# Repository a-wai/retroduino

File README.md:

# RetroDuino

The RetroDuino is an attempt at designing and building an 8-bit microcomputer,
using a 6502 processor, and offering a number of I/O options, as commonly found
on Arduino boards.

## Features

This 130x75mm SBC (Single Board Computer) provides a UART interface, an I2C bus#
and 24 GPIOs.

It includes 31kB of SRAM, 32kB of flash memory (mounted on a ZIF socket for
easier programming), and runs at 8MHz.

## Internals

The RetroDuino includes:

- 1 65C02 processsor w/ 8MHz oscillator
- 1 GAL22V10 for address decoding logic
- 1 AS6C62256 32kB SRAM
- 1 SST39SF010/020/040 flash memory, of which only 32kB is used
- 1 SCC2691 UART controller
- 1 PCF8584 I2C controller
- 1 82C55A peripheral interface providing 24 GPIO lines

It can be powered using a 7-24V DC power supply.

## Current status

This project is still in its infancy: hardware design is complete, but not
tested yet. The next steps are:

- [ ] program and test the GAL logic
- [ ] prototype a flash programmer (probably using a STM32 board)
- [ ] order the board and build the project
- [ ] write the software

## Why?

Why go through so much pain, when hundreds of microcontroller boards are
widely available and so cheap? Because... Well, it's fun!

And as a positive side effect, this is a good way to learn a lot about the
internals of modern microcontrollers, or computers in general.

## Licensing

Copyright 2019, Arnaud Ferraris.

This documentation describes Open Hardware and is licensed under the
CERN OHL v.1.2.

You may redistribute and modify this documentation under the terms of the
[CERN OHL v.1.2](http://ohwr.org/cernohl). This documentation is distributed
WITHOUT ANY EXPRESS OR IMPLIED WARRANTY, INCLUDING OF MERCHANTABILITY,
SATISFACTORY QUALITY AND FITNESS FOR A PARTICULAR PURPOSE.

Please see the CERN OHL v.1.2 for applicable conditions.

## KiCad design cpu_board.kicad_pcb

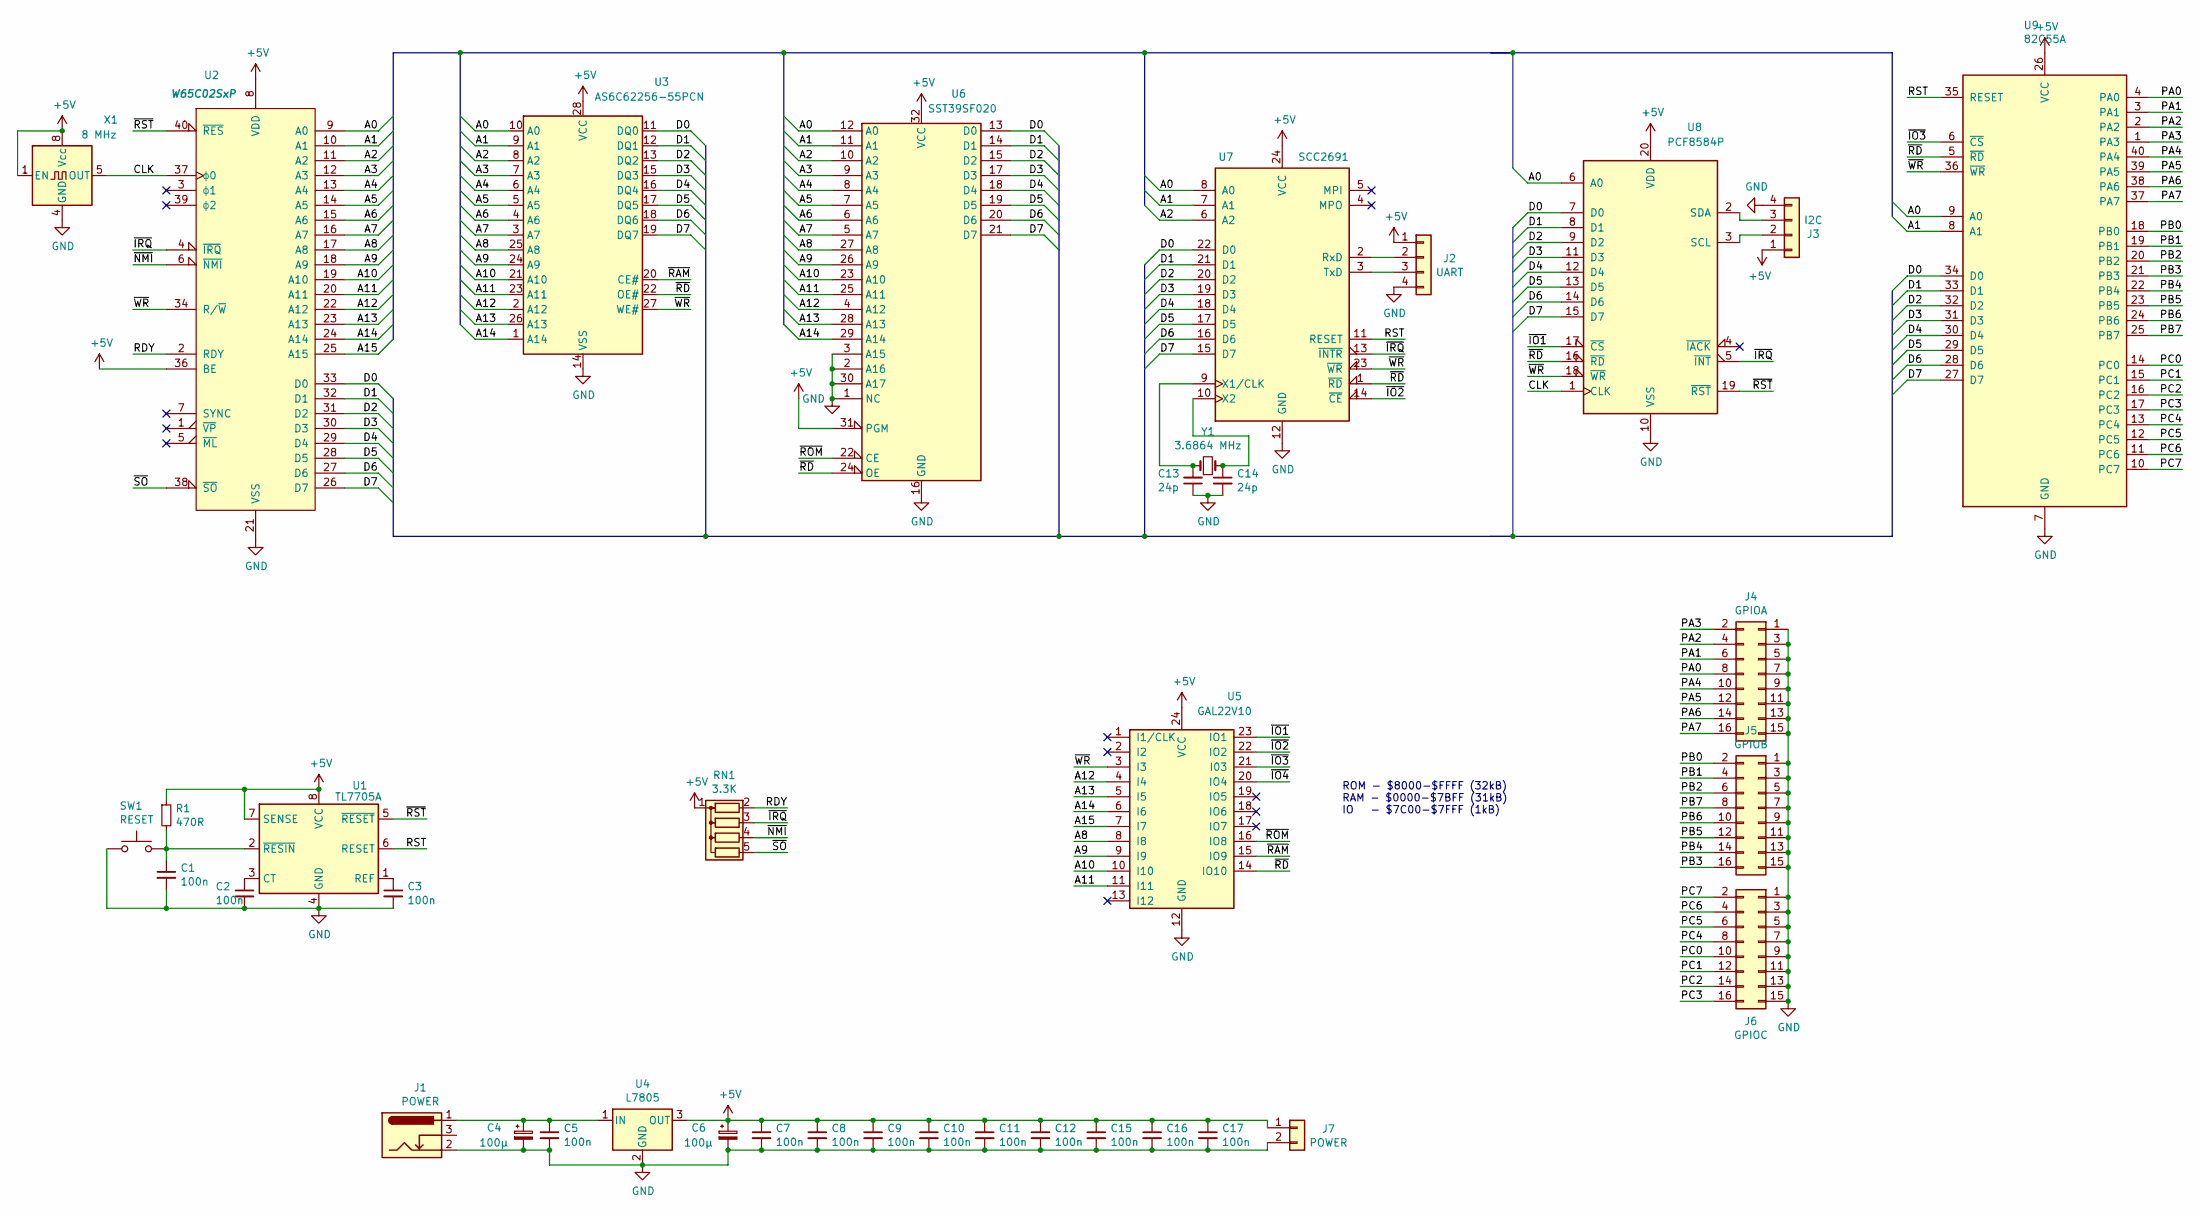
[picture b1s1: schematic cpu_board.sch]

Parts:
C1, C2, C3, C5, C7, C8, C9, C10, C11, C12, C15, C16, C17: 100n; C_Disc_D3.8mm_W2.6mm_P2.50mm
C4, C6: 100µ; CP_Radial_D6.3mm_P2.50mm
C13, C14: 24p; C_Disc_D3.8mm_W2.6mm_P2.50mm
J1: POWER; BarrelJack_Horizontal
J2: UART; PinHeader_1x04_P2.54mm_Vertical
J3: I2C; PinHeader_1x04_P2.54mm_Vertical
J4: GPIOA; PinHeader_2x08_P2.54mm_Vertical
J5: GPIOB; PinHeader_2x08_P2.54mm_Vertical
J6: GPIOC; PinHeader_2x08_P2.54mm_Vertical
J7: POWER; PinHeader_1x02_P2.54mm_Vertical
R1: 470R; R_Axial_DIN0309_L9.0mm_D3.2mm_P12.70mm_Horizontal
RN1: 3.3K; R_Array_SIP5
SW1: RESET; SW_PUSH_6mm
U1: TL7705A; DIP-8_W7.62mm_Socket_LongPads
U2: W65C02SxP; DIP-40_W15.24mm_Socket_LongPads
U3: AS6C62256-55PCN; DIP-28_W15.24mm_Socket_LongPads
U4: L7805; TO-220-3_Vertical
U5: GAL22V10; DIP-24_W7.62mm_Socket_LongPads
U6: SST39SF020; DIP_Socket-32_W11.9_W12.7_W15.24_W17.78_W18.5_3M_232-1285-0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
U7: SCC2691; DIP-24_W7.62mm_Socket_LongPads
U8: PCF8584P; DIP-20_W7.62mm_Socket_LongPads
U9: 82C55A; DIP-40_W15.24mm_Socket_LongPads
X1: 8 MHz; Oscillator_DIP-8_LargePads
Y1: 3.6864 MHz; Crystal_HC49-U_Vertical

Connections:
+5V: C6.1, C7.1, C8.1, C9.1, C10.1, C11.1, C12.1, C15.1, C16.1, C17.1, J2.1, J3.1, J7.1, R1.1, RN1.1 (common), U1.7 (SENSE), U1.8 (VCC), U2.8 (VDD), U2.36 (BE), U3.28 (VCC), U4.3 (OUT), U5.24 (VCC), U6.31 (PGM), U6.32 (VCC), U7.24 (VCC), U8.20 (VDD), U9.26 (VCC), X1.1 (EN), X1.8 (Vcc)
/A0: U2.9 (A0), U3.10 (A0), U6.12 (A0), U7.8 (A0), U8.6 (A0), U9.9 (A0)
/A1: U2.10 (A1), U3.9 (A1), U6.11 (A1), U7.7 (A1), U9.8 (A1)
/A2: U2.11 (A2), U3.8 (A2), U6.10 (A2), U7.6 (A2)
/A3: U2.12 (A3), U3.7 (A3), U6.9 (A3)
/A4: U2.13 (A4), U3.6 (A4), U6.8 (A4)
/A5: U2.14 (A5), U3.5 (A5), U6.7 (A5)
/A6: U2.15 (A6), U3.4 (A6), U6.6 (A6)
/A7: U2.16 (A7), U3.3 (A7), U6.5 (A7)
/A8: U2.17 (A8), U3.25 (A8), U5.8 (I8), U6.27 (A8)
/A9: U2.18 (A9), U3.24 (A9), U5.9 (I9), U6.26 (A9)
/A10: U2.19 (A10), U3.21 (A10), U5.10 (I10), U6.23 (A10)
/A11: U2.20 (A11), U3.23 (A11), U5.11 (I11), U6.25 (A11)
/A12: U2.22 (A12), U3.2 (A12), U5.4 (I4), U6.4 (A12)
/A13: U2.23 (A13), U3.26 (A13), U5.5 (I5), U6.28 (A13)
/A14: U2.24 (A14), U3.1 (A14), U5.6 (I6), U6.29 (A14)
/A15: U2.25 (A15), U5.7 (I7)
/CLK: U2.37 (ϕ0), U8.1 (CLK), X1.5 (OUT)
/D0: U2.33 (D0), U3.11 (DQ0), U6.13 (D0), U7.22 (D0), U8.7 (D0), U9.34 (D0)
/D1: U2.32 (D1), U3.12 (DQ1), U6.14 (D1), U7.21 (D1), U8.8 (D1), U9.33 (D1)
/D2: U2.31 (D2), U3.13 (DQ2), U6.15 (D2), U7.20 (D2), U8.9 (D2), U9.32 (D2)
/D3: U2.30 (D3), U3.15 (DQ3), U6.17 (D3), U7.19 (D3), U8.11 (D3), U9.31 (D3)
/D4: U2.29 (D4), U3.16 (DQ4), U6.18 (D4), U7.18 (D4), U8.12 (D4), U9.30 (D4)
/D5: U2.28 (D5), U3.17 (DQ5), U6.19 (D5), U7.17 (D5), U8.13 (D5), U9.29 (D5)
/D6: U2.27 (D6), U3.18 (DQ6), U6.20 (D6), U7.16 (D6), U8.14 (D6), U9.28 (D6)
/D7: U2.26 (D7), U3.19 (DQ7), U6.21 (D7), U7.15 (D7), U8.15 (D7), U9.27 (D7)
/PA0: J4.8, U9.4 (PA0)
/PA1: J4.6, U9.3 (PA1)
/PA2: J4.4, U9.2 (PA2)
/PA3: J4.2, U9.1 (PA3)
/PA4: J4.10, U9.40 (PA4)
/PA5: J4.12, U9.39 (PA5)
/PA6: J4.14, U9.38 (PA6)
/PA7: J4.16, U9.37 (PA7)
/PB0: J5.2, U9.18 (PB0)
/PB1: J5.4, U9.19 (PB1)
/PB2: J5.6, U9.20 (PB2)
/PB3: J5.16, U9.21 (PB3)
/PB4: J5.14, U9.22 (PB4)
/PB5: J5.12, U9.23 (PB5)
/PB6: J5.10, U9.24 (PB6)
/PB7: J5.8, U9.25 (PB7)
/PC0: J6.10, U9.14 (PC0)
/PC1: J6.12, U9.15 (PC1)
/PC2: J6.14, U9.16 (PC2)
/PC3: J6.16, U9.17 (PC3)
/PC4: J6.8, U9.13 (PC4)
/PC5: J6.6, U9.12 (PC5)
/PC6: J6.4, U9.11 (PC6)
/PC7: J6.2, U9.10 (PC7)
/RDY: RN1.2 (R1), U2.2 (RDY)
/RST: U1.6 (RESET), U7.11 (RESET), U9.35 (RESET)
/~IO1~: U5.23 (IO1), U8.17 (~CS~)
/~IO2~: U5.22 (IO2), U7.14 (~CE~)
/~IO3~: U5.21 (I03), U9.6 (~CS~)
/~IRQ~: RN1.3 (R2), U2.4 (~IRQ), U7.13 (~INTR~), U8.5 (~INT~)
/~NMI~: RN1.4 (R3), U2.6 (~NMI)
/~RAM~: U3.20 (CE#), U5.15 (IO9)
/~RD~: U3.22 (OE#), U5.14 (IO10), U6.24 (OE), U7.1 (~RD~), U8.16 (~RD~), U9.5 (~RD~)
/~ROM~: U5.16 (IO8), U6.22 (CE)
/~RST~: U1.5 (~RESET), U2.40 (~RES), U8.19 (~RST~)
/~SO~: RN1.5 (R4), U2.38 (~SO)
/~WR~: U2.34 (R/~W), U3.27 (WE#), U5.3 (I3), U7.23 (~WR~), U8.18 (~WR~), U9.36 (~WR~)
GND: C1.2, C2.2, C3.2, C4.2, C5.2, C6.2, C7.2, C8.2, C9.2, C10.2, C11.2, C12.2, C13.1, C14.2, C15.2, C16.2, C17.2, J1.2, J2.4, J3.4, J4.1, J4.3, J4.5, J4.7, J4.9, J4.11, J4.13, J4.15, J5.1, J5.3, J5.5, J5.7, J5.9, J5.11, J5.13, J5.15, J6.1, J6.3, J6.5, J6.7, J6.9, J6.11, J6.13, J6.15, J7.2, SW1.1, U1.4 (GND), U2.21 (VSS), U3.14 (VSS), U4.2 (GND), U5.12 (GND), U6.1 (NC), U6.2 (A16), U6.3 (A15), U6.16 (GND), U6.30 (A17), U7.12 (GND), U8.10 (VSS), U9.7 (GND), X1.4 (GND)
unnamed: C1.1, R1.2, SW1.2, U1.2 (~RESIN)
unnamed: C2.1, U1.3 (CT)
unnamed: C3.1, U1.1 (REF)
unnamed: C4.1, C5.1, J1.1, U4.1 (IN)
unnamed: C13.2, U7.9 (X1/CLK), Y1.1
unnamed: C14.1, U7.10 (X2), Y1.2
unnamed: J2.2, U7.2 (RxD)
unnamed: J2.3, U7.3 (TxD)
unnamed: J3.2, U8.3 (SCL)
unnamed: J3.3, U8.2 (SDA)

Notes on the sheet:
ROM - $8000-$FFFF (32kB) RAM - $0000-$7BFF (31kB) IO - $7C00-$7FFF (1kB)

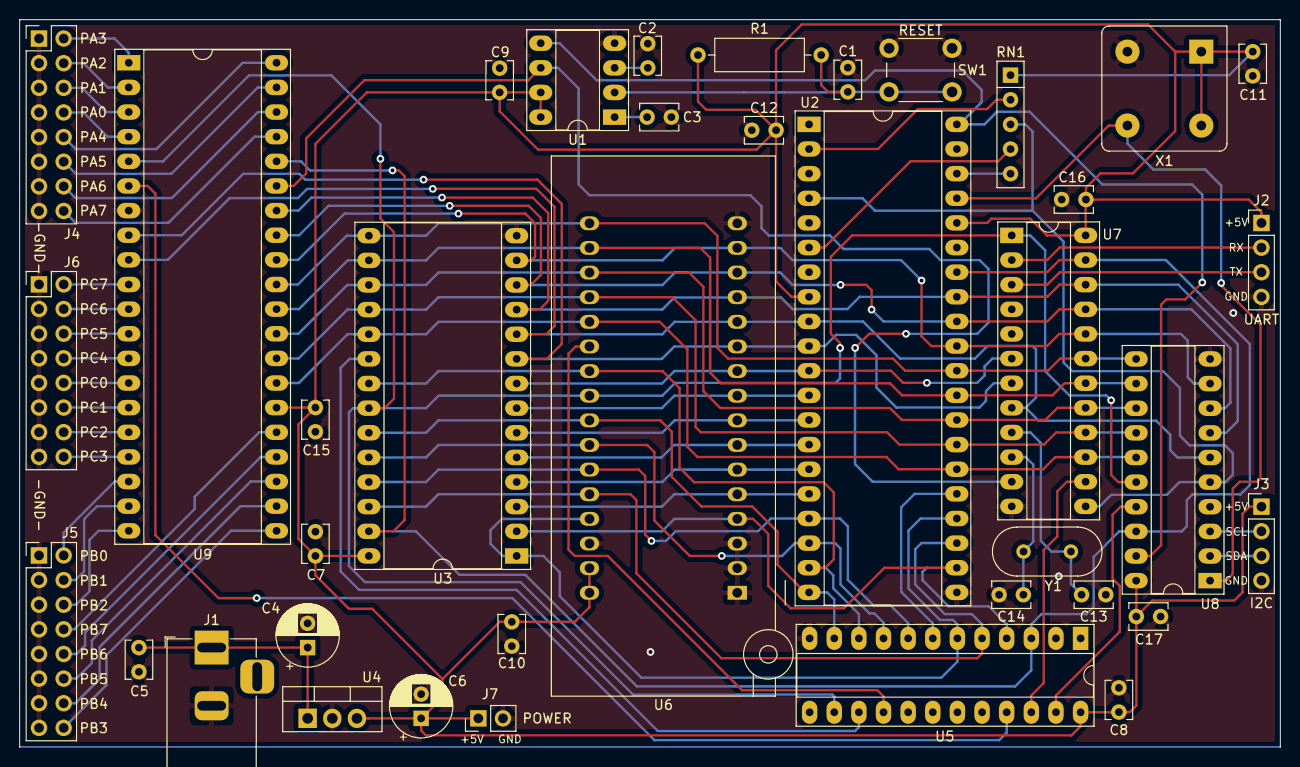
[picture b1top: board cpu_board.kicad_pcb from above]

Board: 2 copper layers, 130.0 x 75.0 mm, 38 parts (0 on the bottom side), 74 nets.

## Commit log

2019-11-21 Initial import
2019-11-21 Fix README
2019-11-27 Fix capacitors footprints & add POWER header
2019-11-28 Add pull-ups for unused CPU inputs
2019-11-28 Add gerber files
2019-11-28 Update 3D rendering
